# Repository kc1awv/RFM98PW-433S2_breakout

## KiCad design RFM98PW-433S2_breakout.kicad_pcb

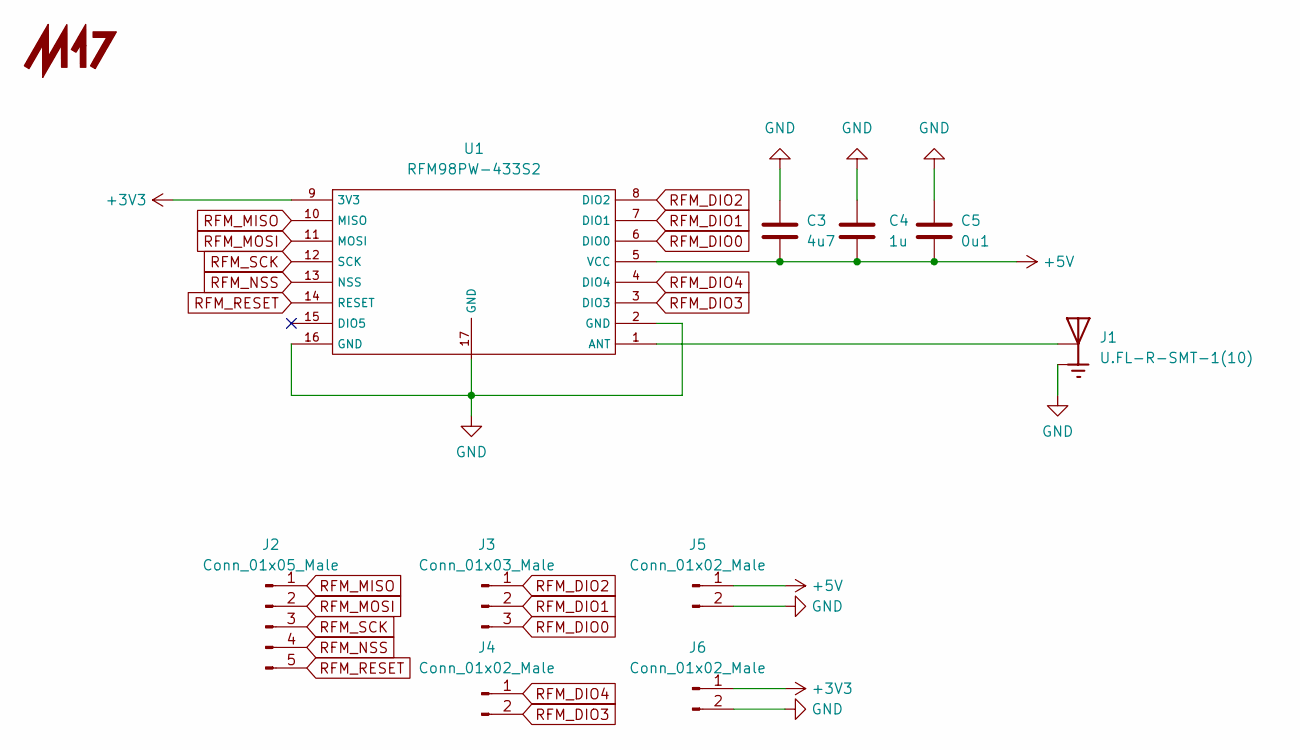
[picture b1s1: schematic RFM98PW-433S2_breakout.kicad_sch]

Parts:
C3: 4u7; C_0603_1608Metric_Pad1.08x0.95mm_HandSolder
C4: 1u; C_0603_1608Metric_Pad1.08x0.95mm_HandSolder
C5: 0u1; C_0603_1608Metric_Pad1.08x0.95mm_HandSolder
J1: U.FL-R-SMT-1(10); HRS_U.FL-R-SMT-1(10)
J2: Conn_01x05_Male; PinHeader_1x05_P2.54mm_Vertical
J3: Conn_01x03_Male; PinHeader_1x03_P2.54mm_Vertical
J4, J5, J6: Conn_01x02_Male; PinHeader_1x02_P2.54mm_Vertical
U1: RFM98PW-433S2

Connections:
+3V3: J6.1, U1.9 (3V3)
+5V: C3.2, C4.2, C5.2, J5.1, U1.5 (VCC)
GND: C3.1, C4.1, C5.1, J1.1, J1.3, J5.2, J6.2, U1.2 (GND), U1.16 (GND), U1.17 (GND)
unnamed: J1.2, U1.1 (ANT)
RFM_DIO0: J3.3, U1.6 (DIO0)
RFM_DIO1: J3.2, U1.7 (DIO1)
RFM_DIO2: J3.1, U1.8 (DIO2)
RFM_DIO3: J4.2, U1.3 (DIO3)
RFM_DIO4: J4.1, U1.4 (DIO4)
RFM_MISO: J2.1, U1.10 (MISO)
RFM_MOSI: J2.2, U1.11 (MOSI)
RFM_NSS: J2.4, U1.13 (NSS)
RFM_RESET: J2.5, U1.14 (RESET)
RFM_SCK: J2.3, U1.12 (SCK)

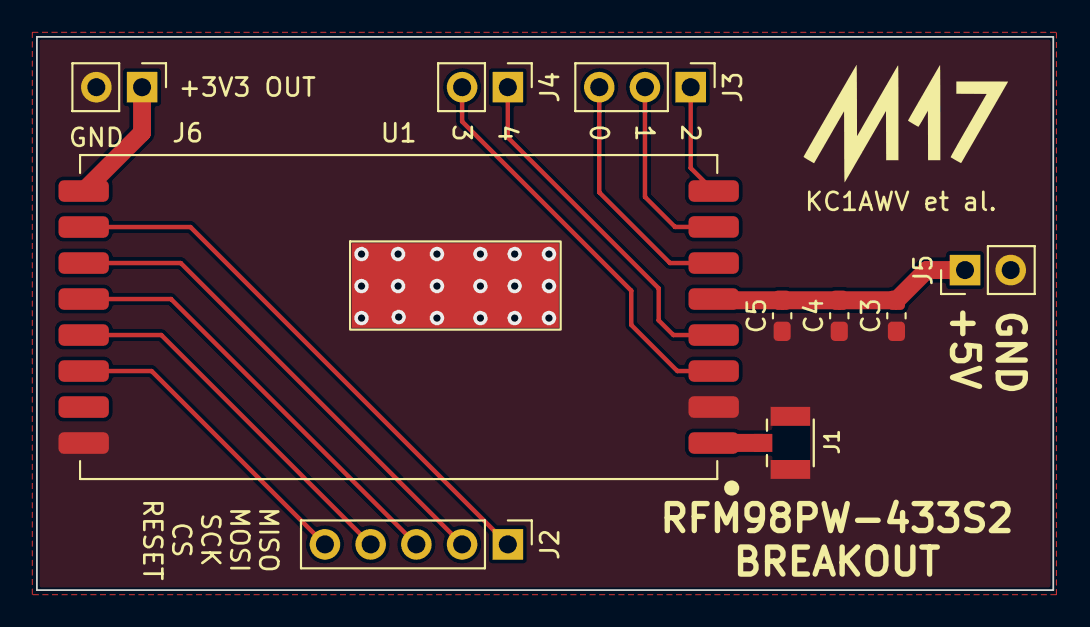
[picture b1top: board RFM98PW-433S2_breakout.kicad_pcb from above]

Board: 2 copper layers, 56.5 x 30.7 mm, 11 parts (0 on the bottom side), 14 nets.

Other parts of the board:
G1: LOGO; M17

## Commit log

2022-03-02 add symbol and footprint
2022-03-03 first run
